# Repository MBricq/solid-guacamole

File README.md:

# solid-guacamole
Intelligent chess board connected to a computer to be able to record live games

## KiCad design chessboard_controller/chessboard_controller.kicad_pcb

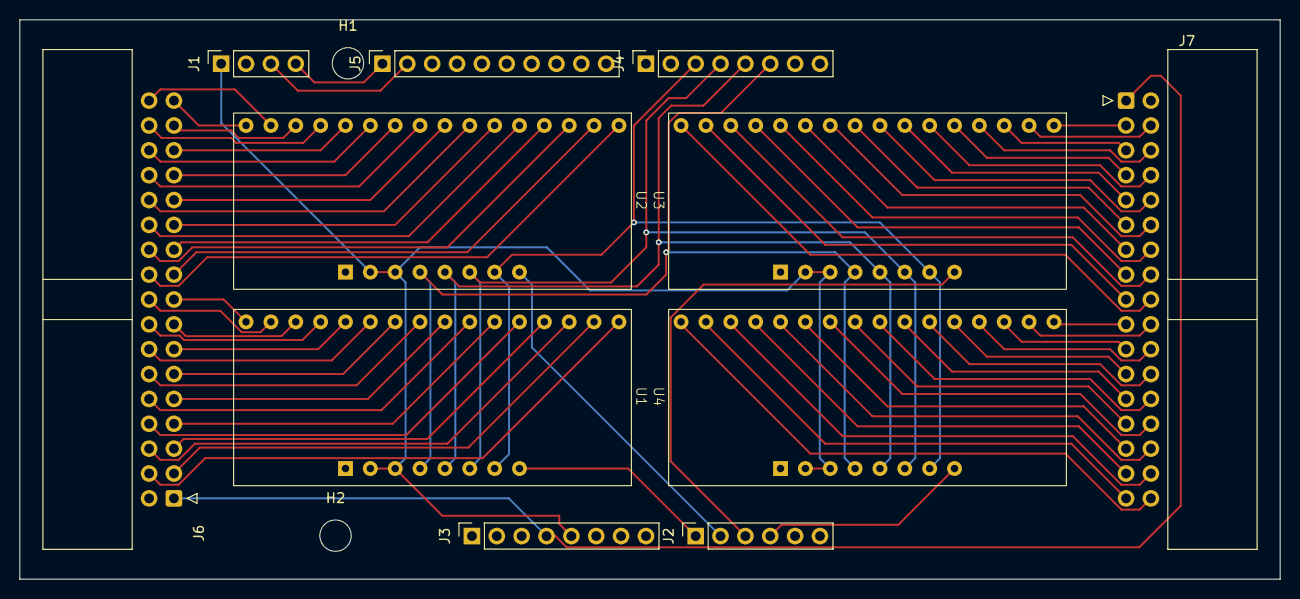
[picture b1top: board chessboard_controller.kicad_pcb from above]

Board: 2 copper layers, 128.8 x 57.2 mm, 13 parts (0 on the bottom side), 77 nets.

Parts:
H1, H2: MountingHole; MountingHole_3.2mm_M3_ISO7380
J1: Conn_01x04; PinSocket_1x04_P2.54mm_Vertical
J2: Conn_01x06; PinSocket_1x06_P2.54mm_Vertical
J3, J4: Conn_01x08; PinSocket_1x08_P2.54mm_Vertical
J5: Conn_01x10; PinSocket_1x10_P2.54mm_Vertical
J6, J7: Conn_02x17_Counter_Clockwise; IDC-Header_2x17_P2.54mm_Horizontal
U1, U2, U3, U4: HV4067; HV5067 Board THT

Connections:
+3.3V: J3.4, J6.1, J7.1
+5V: J1.1, J3.5, U1.6 (EN), U1.7 (VCC), U2.6 (EN), U2.7 (VCC), U3.6 (EN), U3.7 (VCC), U4.6 (EN), U4.7 (VCC)
/S0: J4.6, U1.5 (S0), U2.5 (S0), U3.5 (S0), U4.5 (S0)
/S1: J4.5, U1.4 (S1), U2.4 (S1), U3.4 (S1), U4.4 (S1)
/S2: J4.4, U1.3 (S2), U2.3 (S2), U3.3 (S2), U4.3 (S2)
/S3: J4.3, U1.2 (S3), U2.2 (S3), U3.2 (S3), U4.2 (S3)
/SCL/A5: J1.4, J5.1
/SDA/A4: J1.3, J5.2
/SIG1: J2.1, U1.1 (SIG)
/SIG2: J2.2, U2.1 (SIG)
/SIG3: J2.3, U3.1 (SIG)
/SIG4: J2.4, U4.1 (SIG)
/c101: J6.17, U1.9 (C0)
/c102: J6.18, U1.10 (C1)
/c103: J6.15, U1.11 (C2)
/c104: J6.16, U1.12 (C3)
/c105: J6.13, U1.13 (C4)
/c106: J6.14, U1.14 (C5)
/c107: J6.11, U1.15 (C6)
/c108: J6.12, U1.16 (C7)
/c109: J6.9, U1.17 (C8)
/c110: J6.10, U1.18 (C9)
/c111: J6.7, U1.19 (C10)
/c112: J6.8, U1.20 (C11)
/c113: J6.5, U1.21 (C12)
/c114: J6.6, U1.22 (C13)
/c115: J6.3, U1.23 (C14)
/c116: J6.4, U1.24 (C15)
/c201: J6.33, U2.9 (C0)
/c202: J6.34, U2.10 (C1)
/c203: J6.31, U2.11 (C2)
/c204: J6.32, U2.12 (C3)
/c205: J6.29, U2.13 (C4)
/c206: J6.30, U2.14 (C5)
/c207: J6.27, U2.15 (C6)
/c208: J6.28, U2.16 (C7)
/c209: J6.25, U2.17 (C8)
/c210: J6.26, U2.18 (C9)
/c211: J6.23, U2.19 (C10)
/c212: J6.24, U2.20 (C11)
/c213: J6.21, U2.21 (C12)
/c214: J6.22, U2.22 (C13)
/c215: J6.19, U2.23 (C14)
/c216: J6.20, U2.24 (C15)
/c301: J7.18, U3.9 (C0)
/c302: J7.17, U3.10 (C1)
/c303: J7.16, U3.11 (C2)
/c304: J7.15, U3.12 (C3)
/c305: J7.14, U3.13 (C4)
/c306: J7.13, U3.14 (C5)
/c307: J7.12, U3.15 (C6)
/c308: J7.11, U3.16 (C7)
/c309: J7.10, U3.17 (C8)
/c310: J7.9, U3.18 (C9)
/c311: J7.8, U3.19 (C10)
/c312: J7.7, U3.20 (C11)
/c313: J7.6, U3.21 (C12)
/c314: J7.5, U3.22 (C13)
/c315: J7.4, U3.23 (C14)
/c316: J7.3, U3.24 (C15)
/c401: J7.34, U4.9 (C0)
/c402: J7.33, U4.10 (C1)
/c403: J7.32, U4.11 (C2)
/c404: J7.31, U4.12 (C3)
/c405: J7.30, U4.13 (C4)
/c406: J7.29, U4.14 (C5)
/c407: J7.28, U4.15 (C6)
/c408: J7.27, U4.16 (C7)
/c409: J7.26, U4.17 (C8)
/c410: J7.25, U4.18 (C9)
/c411: J7.24, U4.19 (C10)
/c412: J7.23, U4.20 (C11)
/c413: J7.22, U4.21 (C12)
/c414: J7.21, U4.22 (C13)
/c415: J7.20, U4.23 (C14)
/c416: J7.19, U4.24 (C15)
GND: J1.2, J3.6, J3.7, J5.4, J6.2, J7.2, U1.8 (GND), U2.8 (GND), U3.8 (GND), U4.8 (GND)

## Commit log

2024-03-25 KiCAD base project
2024-03-29 First version of layout
